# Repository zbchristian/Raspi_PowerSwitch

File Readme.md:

Power Switch HAT for Raspberry Pi based on Arduino Tiny
=======================================================
Per default the Raspberry Pi is powered via the USB port, but no power switch exists for a controlled shutdown.

This device connects to the GPIO and power pins of the extension port.

An Arduino Tiny (Digispark) controls the 5V supply voltage via an MOSFET switch (up to 3A).  
In addition the Arduino 
 - reads the status of the Raspberry Pi on `GPIO 27`. Pulled low while the Raspberry Pi is running, 
 - sets the shutdown request on `GPIO 17` in case the button is pressed, 
 - disconnects the 5V supply from the Raspberry Pi after a predefined timeout. This allows for a controlled shutdown and avoids a possible corruption of the SD-card. 

The device can be powered by a 5V supply, or a DC-DC converter can be added to allow the powering directly from a 12V (or higher) supply (e.g. car battery).
The Arduino is supplied by a 3.3V regulator on the board. This ensures, that the signals of the Arduino and the Raspberry Pi are compatible.

The default power button is a touch button connected via a 1MOhm resistor to Port 4 and sensed via Port 2 of the ATTINY85.
A standard button can be connected to Port 4 as well, but requires to adapt the code.

This device has been developped for the powering of a Raspberry Pi 3a used as Wireless access point (installed is [RaspAP](https://raspap.com/) ) in a very flat case. The Raspberry Pi 
is used in a Camper Van to connect to camp ground wireless networks or LTE/4G. The device is powered in this case by 12V.   

*Power switch installed on a Raspberry Pi 3a, including a touch button (metal pin)*

The power required by the device, when the Raspberry Pi is switched off, is about 20mW (ca. 1.5mA@12V).

Required Hardware Components
-------------------
 - Arduino Tiny - Digispark board. The version with the micro USB port is preferred. This allows to program the board while soldered to the PCB.
 - DC-DC converter in case the the input voltage is higher than 5V.
 - PCB and the required components (SMD components and a pin header)
 - MOSFET transistor 
   - Suitable types: FDN360P, TMS2305, DMT3098 (package: SOT-23). All allow to switch up to 2A continuously, which should still be fine for a Raspberry Pi 4.
   - For higher currents an IRF9310 (up to 16A) could be used, but this comes in a different package (SO-8) and the layout has to be changed accordingly.

Software
--------
The Arduino IDE is used for the programming of the Arduino Tiny. See the header of the program file for more details of the program flow.  
The package `CapacitiveSensor` is required, if the above mentioned touch button is used.

On the Raspberry Pi side, you need to add the following lines to `/boot/config.txt`
````
# Request shutdown by setting GPIO 17 to HIGH
dtoverlay=gpio-shutdown,gpio_pin=17,active_low=0,gpio_pull=down
# GPIO 27 flags the shutdown of the system
gpio=27=op,dl
````

Board Design
------------
Schematic and board design are available in the Autodesk EAGLE format. The library file contains the non-standard components (Arduino Tiny, DC-DC converter). Gerber files, Bill of material and placement files are available as well.

The board connects to the first 14 pins of the extension port of the Raspberry Pi via a pin header. The header connector is installed to the bottom of the board. A low profile connector 
is recommended. For the Raspberry Pi 3a in its default case, the pins had to be shortened a bit and a header with a height of only 8.6mm has been used.  

*Arduino Tiny soldered to the Power Switch board*

The design of the board is somewhat special, because a very flat layout is needed to fit into a standard case. 
Therefore the Arduino Tiny is soldered to large SMD pads. This is not difficult, but requires some soldering experience. It might help to solder a solid wire (0.4mm) to the through holes of the 
Arduino Tiny, bend the wires by 90° to the outside, cut to length and solder the ends of the wires to the SMD pads.  
Before soldering, add an isolating tape to the bottom of the Arduino to avoid shorts. 

On the bottom side of the board a solder jumper sets the source of the power. A closed jumper connects the input voltage from the pin header directly to the Raspberry Pi and the 
on board regulator. For higher voltages, e.g. 12V from a car battery, the jumper should be left open and a mini DC-DC converter is soldered to the SMD pads on the bottom side. The output voltage of the DC-DC converter
should be set to 5V. Again add an isolating tape to the bottom of the DC-DC converter to avoid shorts. 

*Bottom side of the Power Switch: left side for 5V input voltage with the solder jumper closed. On the right side the DC-DC converter is installed for a higher voltage*

On the bottom side you find in addition 3 solder pads to connect a button. One of the pads carries either the signal of Port 2 or ground. This can be selected by the solder jumper on the top.
 - Passive button: connect to Port 4 and the P2/GND pad and select GND with the solder jumper on the top.
 - Software based touch button: connect to P4 and P2 (select P2 with the solder jumper on top).
 - Hardware touch button: signal connected to P4. Powering by 3.3V and GND pad.

The software based touch button is implemented in the code. The other options require an adaption of the code.  

Quiescent Power Consumption
--------------------------
The Arduino Tiny will draw up to 10mA when powered by the onboard 5V regulator (78X05). This is mainly due to the quiescent current of the regulator itself , the power LED 
and the 1.5kOhm pull-up resistor connected to port 3 of the ATTINY85 (needed for the USB programming). The ATTINY85 with reduced frequency of about 1MHz
utilizes only a few hundred micro Amps. 

Reduce the required power by
 - run the ATTINY85 at a low frequency (e.g. 1MHz)
 - use an external 3.3V regulator with low quiescent current (here MCP1703). Remove the 78X05 from the board (might not be necessary).
 - either remove the power LED, or change at least the series resistor from 1kOhm to 10kOhm
 - remove the LED attached to Port 1, or increase the series resistor to 10kOhm
 - disconnect the 1.5kOhm resistor from the power rail of the ATTINY85 and connect it to the USB 5V line (USB connector side of the corresponding Schottky diode).

For a 5V powered system, this should bring the qiescent current down well below 1mA at 5V.
With the installed DC-DC converter the current stays at about 1.5mA at 12V (18mW).

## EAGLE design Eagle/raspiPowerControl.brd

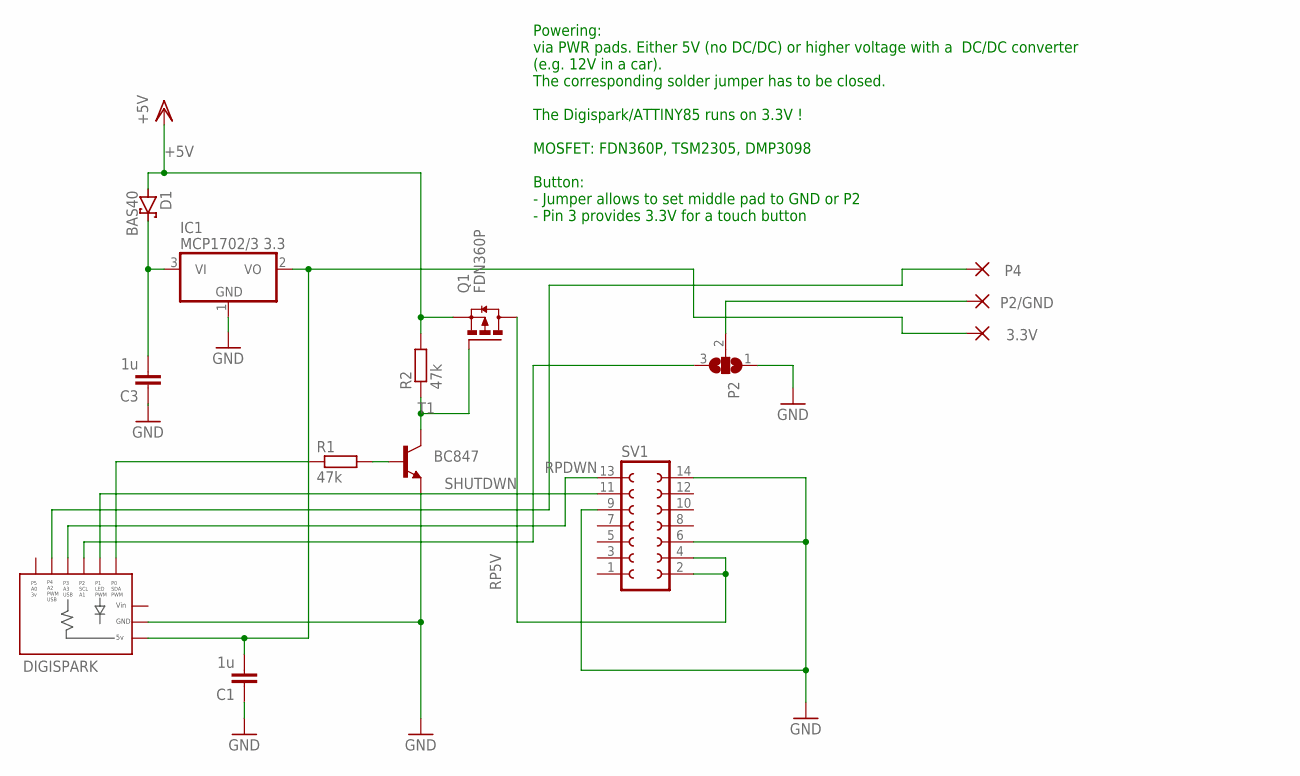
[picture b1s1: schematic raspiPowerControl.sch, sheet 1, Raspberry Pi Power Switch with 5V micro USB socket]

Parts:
3.3V: WIREPADSMD5-1,8; 5-1,8
C1, C3: 1u; C0805
D1: BAS40; SOT23
DIGISPARK: DIGISPARKDIGISPARK-SMD; DIGISPARK-SMD
IC1: MCP1702/3 3.3; SOT23
P2: SJ2W; SJ_2
P2/GND, P4: WIREPADSMD5-1,8; 5-1,8
Q1: FDN360P; SUPER-SOT3
R1, R2: 47k; M0805
SV1: FE07-2
T1: BC847; SOT23

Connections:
3V3: 3.3V.1, C1.2, DIGISPARK.5V, IC1.2 (VO)
+5V: D1.1 (A), Q1.2 (S), R2.2; also elsewhere on the board
BUT2: P2.2, P2/GND.1
BUT4: DIGISPARK.P4, P4.1
GND: C1.1, C3.1, DIGISPARK.GND, IC1.1 (GND), P2.1, SV1.6, SV1.9, SV1.14, T1.2 (E); also elsewhere on the board
unnamed: C3.2, D1.3 (C), IC1.3 (VI)
unnamed: Q1.1 (G), R2.1, T1.3 (C)
unnamed: R1.2, T1.1 (B)
P2: DIGISPARK.P2, P2.3
RP5V: Q1.3 (D), SV1.2, SV1.4
RPDWN: DIGISPARK.P3, SV1.13
SHUTDWN: DIGISPARK.P1, SV1.11
SWPWR: DIGISPARK.P0, R1.1
VIN: DIGISPARK.VIN

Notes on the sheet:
Powering: via PWR pads. Either 5V (no DC/DC) or higher voltage with a DC/DC converter (e.g. 12V in a car). The corresponding solder jumper has to be closed. The Digispark/ATTINY85 runs on 3.3V ! MOSFET: FDN360P, TSM2305, DMP3098 Button: - Jumper allows to set middle pad to GND or P2 - Pin 3 provide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

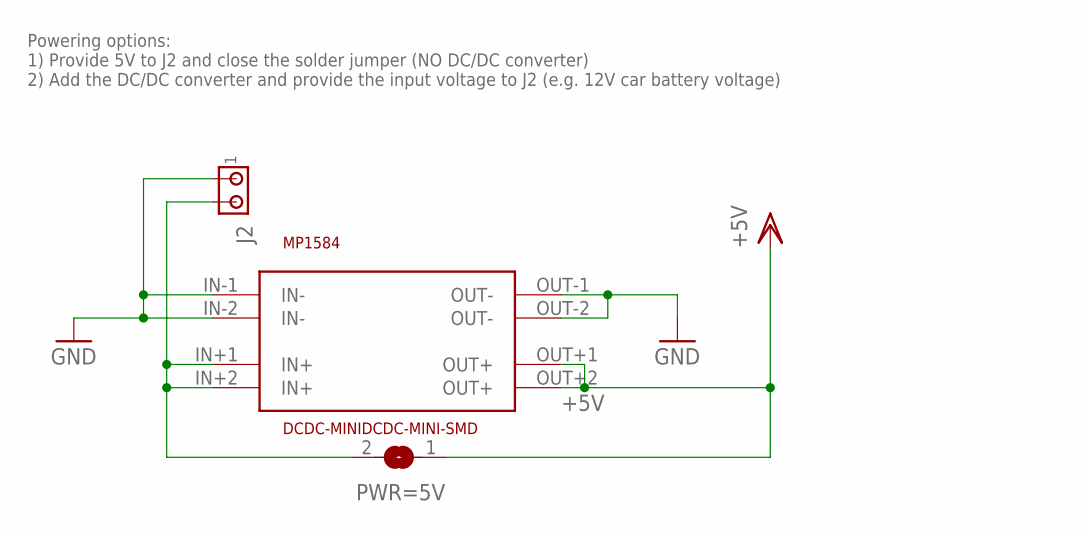
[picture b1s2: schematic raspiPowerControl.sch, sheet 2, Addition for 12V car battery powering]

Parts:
J2: MTA02-100; 10X02MTA
MP1584: DCDC-MINIDCDC-MINI-SMD; DCDC-MINI-SMD
PWR=5V: SJ

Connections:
+5V: MP1584.OUT+1 (OUT+), MP1584.OUT+2 (OUT+), PWR=5V.1; also elsewhere on the board
GND: J2.1, MP1584.IN-1 (IN-), MP1584.IN-2 (IN-), MP1584.OUT-1 (OUT-), MP1584.OUT-2 (OUT-); also elsewhere on the board
PWR: J2.2, MP1584.IN+1 (IN+), MP1584.IN+2 (IN+), PWR=5V.2

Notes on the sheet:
Powering options: 1) Provide 5V to J2 and close the solder jumper (NO DC/DC converter) 2) Add the DC/DC converter and provide the input voltage to J2 (e.g. 12V car battery voltage)

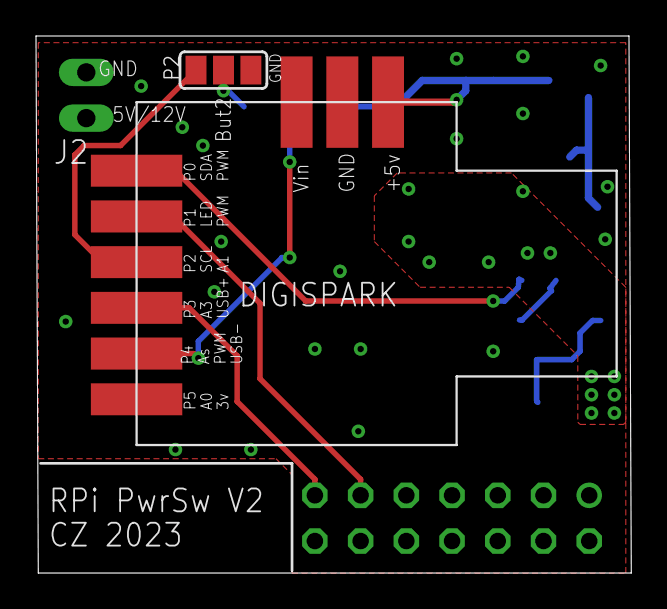
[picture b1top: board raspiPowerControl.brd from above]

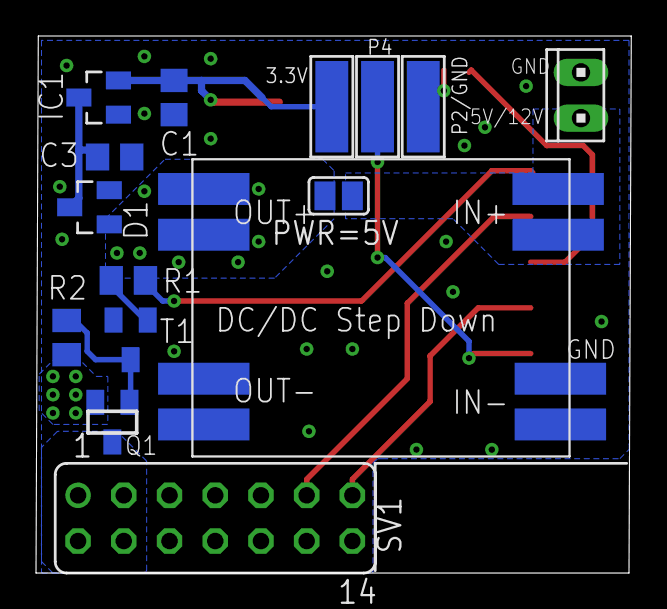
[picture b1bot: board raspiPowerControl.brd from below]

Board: 2 copper layers, 33.1 x 29.8 mm, 17 parts (15 on the bottom side), 14 nets.

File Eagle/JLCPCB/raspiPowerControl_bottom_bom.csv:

Comment,Designator,Footprint,LCSC Part #
1u,3.3V P2/GND P4 PWR=5V C1 C3,C0805,
47k,R1 R2,M0805,
BAS40,D1,SOT23,
BC847,T1,SOT23,
DCDC-MINIDCDC-MINI-SMD,MP1584,DCDC-MINI-SMD,
FDN360P,Q1,SUPER-SOT3,
MCP1702/3 3.3,IC1,SOT23,

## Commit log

2023-09-10 Initial commit from ATTINY85 based Power switch
2023-09-10 Move arduino source to sub folder
2023-09-10 Add button and change setup
2023-09-11 Revert to original
2023-11-04 Add Eagle design
2023-11-04 Update Eagle
2023-11-04 Add regulator to design
2023-12-01 Add DC/DC converter to design
2023-12-03 Modified layout
2023-12-04 Smaller pads for button
2023-12-04 Add JLC PCB and assembly files
2023-12-16 Correct layout
2023-12-17 Update layout
2023-12-22 Update board size and touch sensor thresh
2024-01-01 Update comment
2024-01-02 Add Readme.md
2024-01-02 Really add Readme.md
2024-01-02 Add images
2024-01-02 Include images in Readme.md
2024-01-02 Adjust image sizes
2024-01-02 Add captions to images
2024-01-02 Add line breaks
2024-01-03 Add schematic as PDF
2024-01-03 Remove image of original prototype
2024-01-26 Correct comment in source code
2024-01-26 Update comments
